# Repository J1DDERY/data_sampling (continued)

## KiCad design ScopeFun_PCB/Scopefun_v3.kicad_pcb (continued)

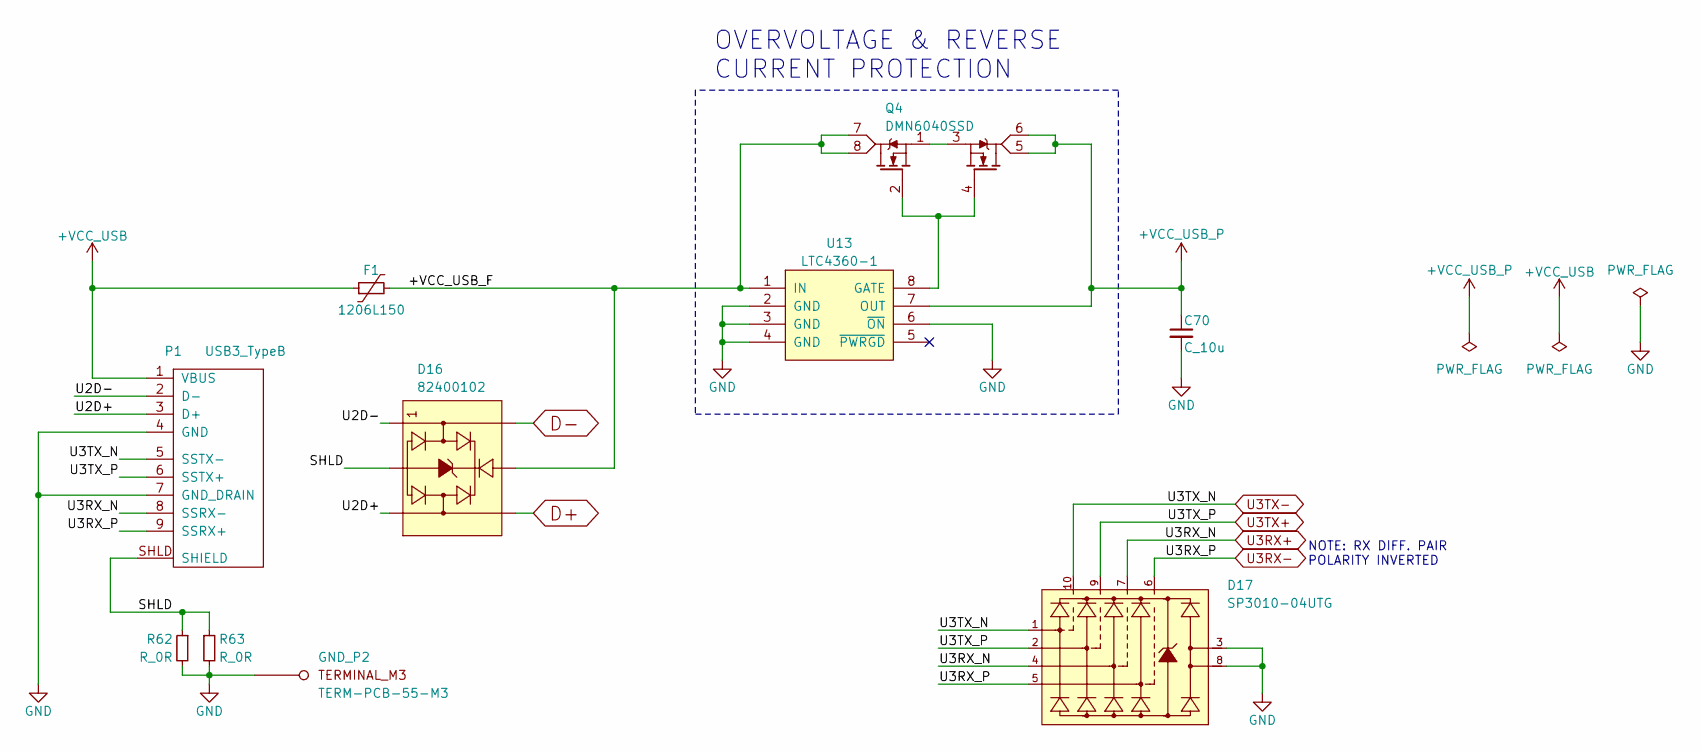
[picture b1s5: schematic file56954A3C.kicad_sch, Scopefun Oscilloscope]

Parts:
C70: C_10u; C_0603; MFG Part# GRM188R60J106KE47D
D16: 82400102; SOT23-6; MFG Part# 82400102
D17: SP3010-04UTG; uDFN-10; MFG Part# SP3010-04UTG
F1: 1206L150; R_1206; MFG Part# 1206L150THWR
GND_P2: TERM-PCB-55-M3; MFG Part# PCB-55(M3)
P1: USB3_TypeB; MFG Part# 692221030100
Q4: DMN6040SSD; SOIC8; MFG Part# DMN6040SSD-13
R62, R63: R_0R; R_0805; MFG Part# ERJ-6GEY0R00V
U13: LTC4360-1; SC70; MFG Part# LTC4360CSC8-1

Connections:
+VCC_USB: F1.1, P1.1 (VBUS)
+VCC_USB_P: C70.1, Q4.5 (D2), Q4.6 (D2), U13.7 (OUT); also elsewhere on the board
/USB Port/+VCC_USB_F: D16.5 (VDD), F1.2, Q4.7 (D1), Q4.8 (D1), U13.1 (IN)
/USB Port/SHLD: D16.2 (GND), P1.SHLD (SHIELD), R62.1, R63.1
/USB Port/U2D+: D16.3 (IO2), P1.3 (D+)
/USB Port/U2D-: D16.1 (IO1), P1.2 (D-)
D+: D16.4 (IO2); also elsewhere on the board
D-: D16.6 (IO1); also elsewhere on the board
GND: C70.2, D17.3 (IO2), D17.8 (IO1), GND_P2.1 (1_1), P1.4 (GND), P1.7 (GND_DRAIN), R62.2, R63.2, U13.2 (GND), U13.3 (GND), U13.4 (GND), U13.6 (~ON); also elsewhere on the board
unnamed: Q4.2 (G1), Q4.4 (G2), U13.8 (GATE)
unnamed: Q4.1 (S1), Q4.3 (S2)
U3RX+: D17.4 (IO2), D17.7 (IO1), P1.8 (SSRX-); also elsewhere on the board
U3RX-: D17.5 (VDD), D17.6 (IO1), P1.9 (SSRX+); also elsewhere on the board
U3TX+: D17.2 (GND), D17.9 (IO1), P1.6 (SSTX+); also elsewhere on the board
U3TX-: D17.1 (IO1), D17.10 (IO1), P1.5 (SSTX-); also elsewhere on the board

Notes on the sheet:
NOTE: RX DIFF. PAIR POLARITY INVERTED
OVERVOLTAGE & REVERSE CURRENT PROTECTION

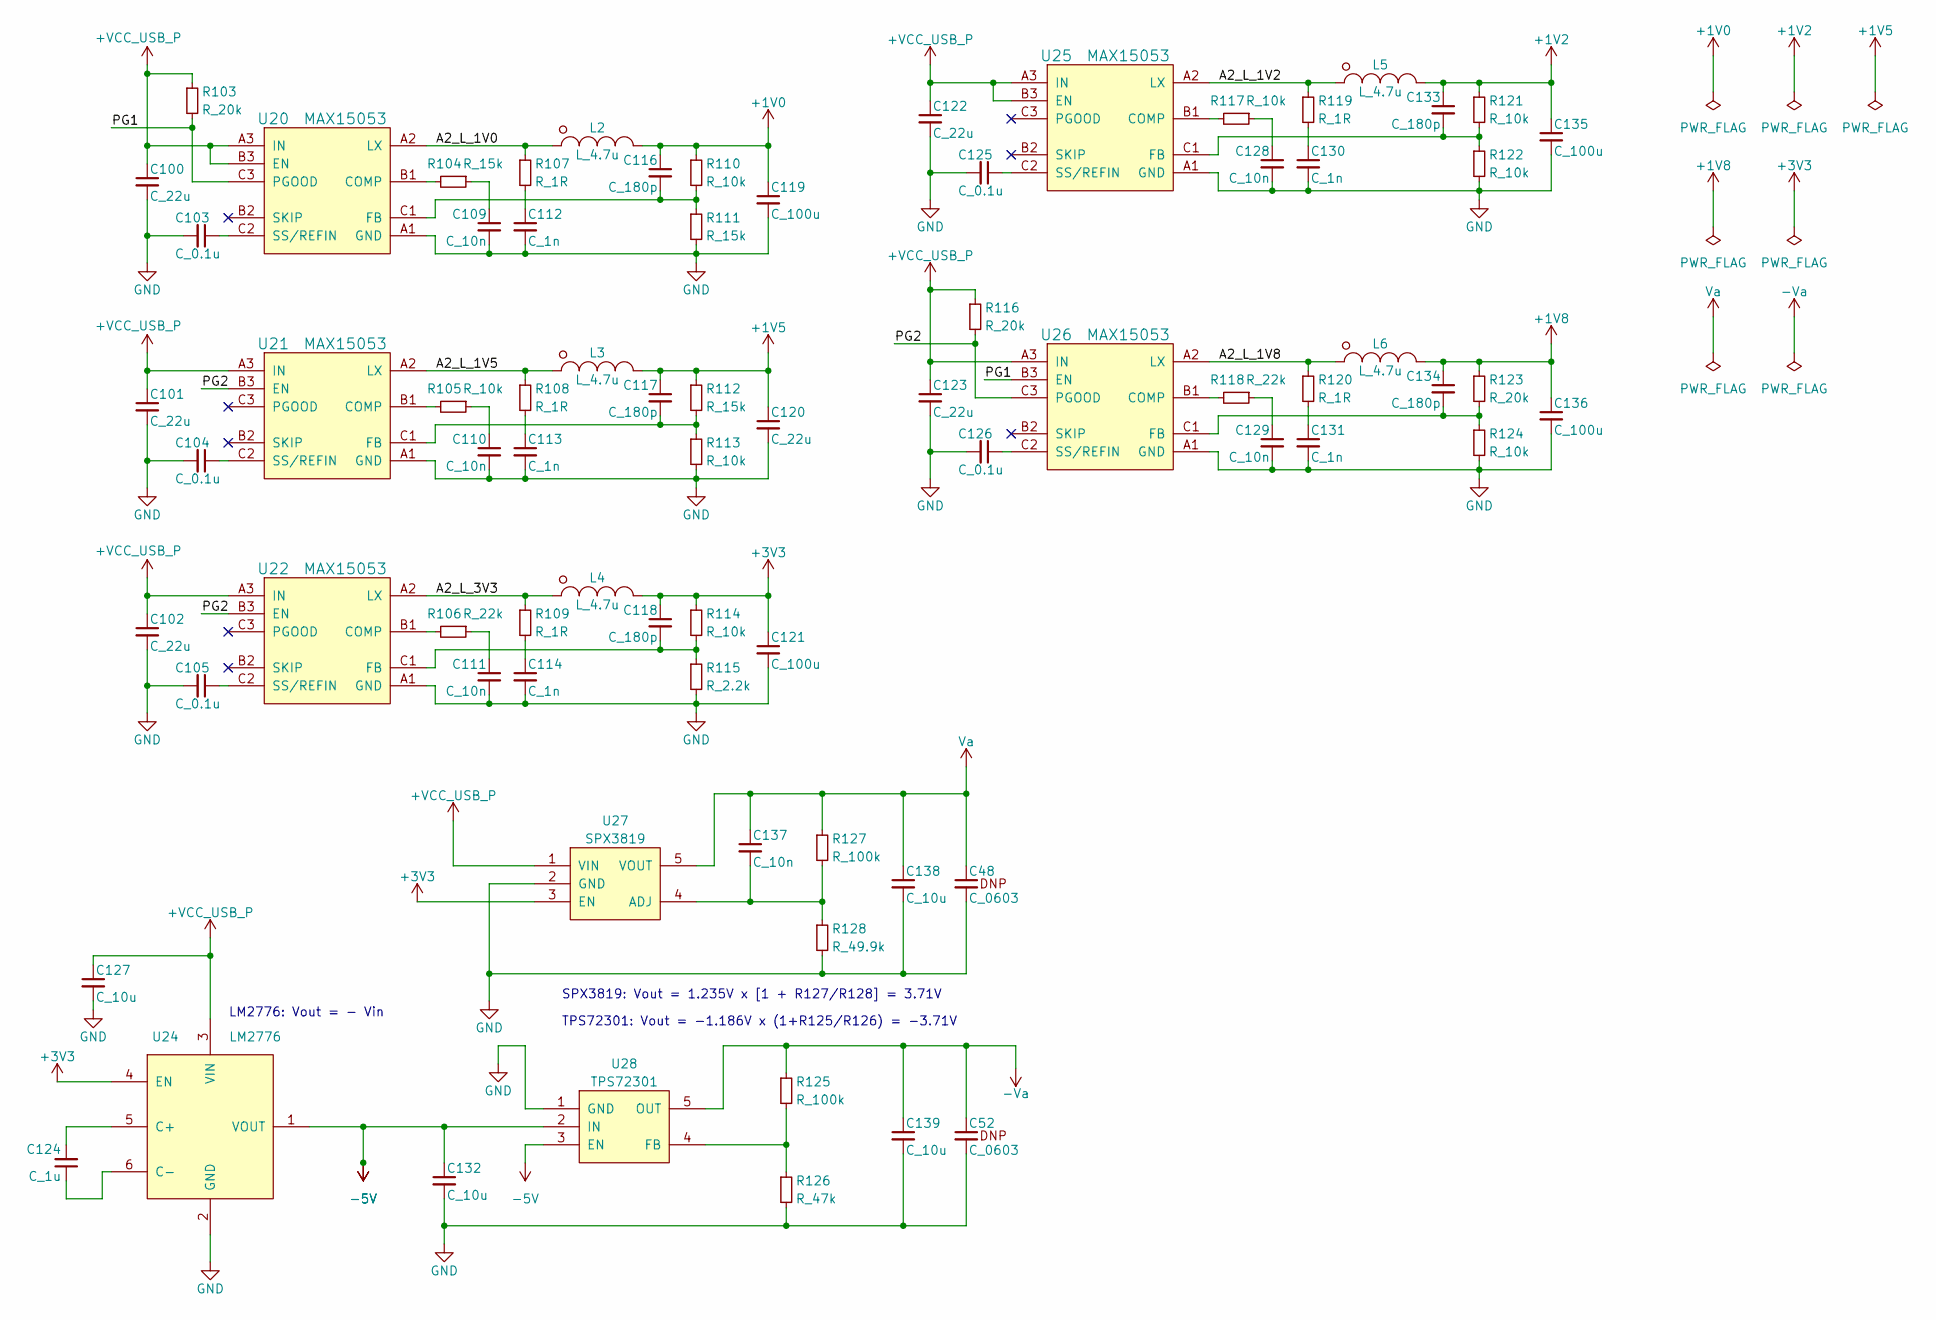
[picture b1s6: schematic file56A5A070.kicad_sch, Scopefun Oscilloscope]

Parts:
C48, C52: C_0603
C100, C101, C102, C120, C122, C123: C_22u; C_0805; MFG Part# LMK212BBJ226MG-T
C103, C104, C105, C125, C126: C_0.1u; C_0603; MFG Part# C0603C104K4RACTU
C109, C110, C111, C128, C129, C137: C_10n; C_0603; MFG Part# GRM1885C1H103JA01D
C112, C113, C114, C130, C131: C_1n; C_0603; MFG Part# C1608X7R1H102K080AE
C116, C117, C118, C133, C134: C_180p; C_0603; MFG Part# C0603C181J5GACTU
C119, C121, C135, C136: C_100u; C_1210; MFG Part# 12106D107MAT2A
C124: C_1u; C_0603; MFG Part# C0603C105K9PACTU
C127, C132, C138, C139: C_10u; C_0603; MFG Part# GRM188R60J106KE47D
L2, L3, L4, L5, L6: L_4.7u; L_NRS; MFG Part# NRS5030T4R7MMGJ
R103, R116, R123: R_20k; R_0603; MFG Part# ERJ-3EKF2002V
R104, R111, R112: R_15k; R_0603; MFG Part# ERJ-3EKF1502V
R105, R110, R113, R114, R117, R121, R122, R124: R_10k; R_0603; MFG Part# ERJ-3EKF1002V
R106, R118: R_22k; R_0603; MFG Part# ERJ-3EKF2202V
R107, R108, R109, R119, R120: R_1R; R_0603; MFG Part# ERJ-3GEYJ1R0V
R115: R_2.2k; R_0603; MFG Part# ERJ-3EKF2201V
R125, R127: R_100k; R_0603; MFG Part# ERJ-3EKF1003V
R126: R_47k; R_0603; MFG Part# ERJ-3EKF4702V
R128: R_49.9k; R_0603; MFG Part# ERJ-3EKF4992V
U20, U21, U22, U25, U26: MAX15053; WLP-9; MFG Part# MAX15053EWL+T
U24: LM2776; SOT23-6; MFG Part# LM2776DBVR
U27: SPX3819; SOT23-5_EXAR; MFG Part# SPX3819M5-L/TR
U28: TPS72301; SOT23-5; MFG Part# TPS72301DBVR

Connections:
+1V0: C116.1, C119.1, L2.2, R110.1; also elsewhere on the board
+1V2: C133.1, C135.1, L5.2, R121.1; also elsewhere on the board
+1V5: C117.1, C120.1, L3.2, R112.1; also elsewhere on the board
+1V8: C134.1, C136.1, L6.2, R123.1; also elsewhere on the board
+3V3: C118.1, C121.1, L4.2, R114.1, U24.4 (EN), U27.3 (EN); also elsewhere on the board
+VCC_USB_P: C100.1, C101.1, C102.1, C122.1, C123.1, C127.1, R103.1, R116.1, U20.A3 (IN), U20.B3 (EN), U21.A3 (IN), U22.A3 (IN), U24.3 (VIN), U25.A3 (IN), U25.B3 (EN), U26.A3 (IN), U27.1 (VIN); also elsewhere on the board
-5V: C132.1, U24.1 (VOUT), U28.2 (IN), U28.3 (EN)
-Va: C52.1, C139.1, R125.1, U28.5 (OUT); also elsewhere on the board
/POWER SUPPLY/A2_L_1V0: L2.1, R107.1, U20.A2 (LX)
/POWER SUPPLY/A2_L_1V2: L5.1, R119.1, U25.A2 (LX)
/POWER SUPPLY/A2_L_1V5: L3.1, R108.1, U21.A2 (LX)
/POWER SUPPLY/A2_L_1V8: L6.1, R120.1, U26.A2 (LX)
/POWER SUPPLY/A2_L_3V3: L4.1, R109.1, U22.A2 (LX)
/POWER SUPPLY/PG1: R103.2, U20.C3 (PGOOD), U26.B3 (EN)
/POWER SUPPLY/PG2: R116.2, U21.B3 (EN), U22.B3 (EN), U26.C3 (PGOOD)
GND: C48.2, C52.2, C100.2, C101.2, C102.2, C103.2, C104.2, C105.2, C109.2, C110.2, C111.2, C112.2, C113.2, C114.2, C119.2, C120.2, C121.2, C122.2, C123.2, C125.2, C126.2, C127.2, C128.2, C129.2, C130.2, C131.2, C132.2, C135.2, C136.2, C138.2, C139.2, R111.2, R113.2, R115.2, R122.2, R124.2, R126.2, R128.2, U20.A1 (GND), U21.A1 (GND), U22.A1 (GND), U24.2 (GND), U25.A1 (GND), U26.A1 (GND), U27.2 (GND), U28.1 (GND); also elsewhere on the board
unnamed: C109.1, R104.1
unnamed: C110.1, R105.1
unnamed: C111.1, R106.1
unnamed: C112.1, R107.2
unnamed: C113.1, R108.2
unnamed: C114.1, R109.2
unnamed: C128.1, R117.1
unnamed: C129.1, R118.1
unnamed: C130.1, R119.2
unnamed: C131.1, R120.2
unnamed: R104.2, U20.B1 (COMP)
unnamed: C116.2, R110.2, R111.1, U20.C1 (FB)
unnamed: C103.1, U20.C2 (SS/REFIN)
unnamed: R105.2, U21.B1 (COMP)
unnamed: C117.2, R112.2, R113.1, U21.C1 (FB)
unnamed: C104.1, U21.C2 (SS/REFIN)
unnamed: R106.2, U22.B1 (COMP)
unnamed: C118.2, R114.2, R115.1, U22.C1 (FB)
unnamed: C105.1, U22.C2 (SS/REFIN)
unnamed: C124.2, U24.5 (C+)
unnamed: C124.1, U24.6 (C-)
unnamed: R117.2, U25.B1 (COMP)
unnamed: C133.2, R121.2, R122.1, U25.C1 (FB)
unnamed: C125.1, U25.C2 (SS/REFIN)
unnamed: R118.2, U26.B1 (COMP)
unnamed: C134.2, R123.2, R124.1, U26.C1 (FB)
unnamed: C126.1, U26.C2 (SS/REFIN)
unnamed: C137.2, R127.2, R128.1, U27.4 (ADJ)
unnamed: R125.2, R126.1, U28.4 (FB)
Va: C48.1, C137.1, C138.1, R127.1, U27.5 (VOUT); also elsewhere on the board

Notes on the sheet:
SPX3819: Vout = 1.235V x [1 + R127/R128] = 3.71V
TPS72301: Vout = -1.186V x (1+R125/R126) = -3.71V
LM2776: Vout = - Vin

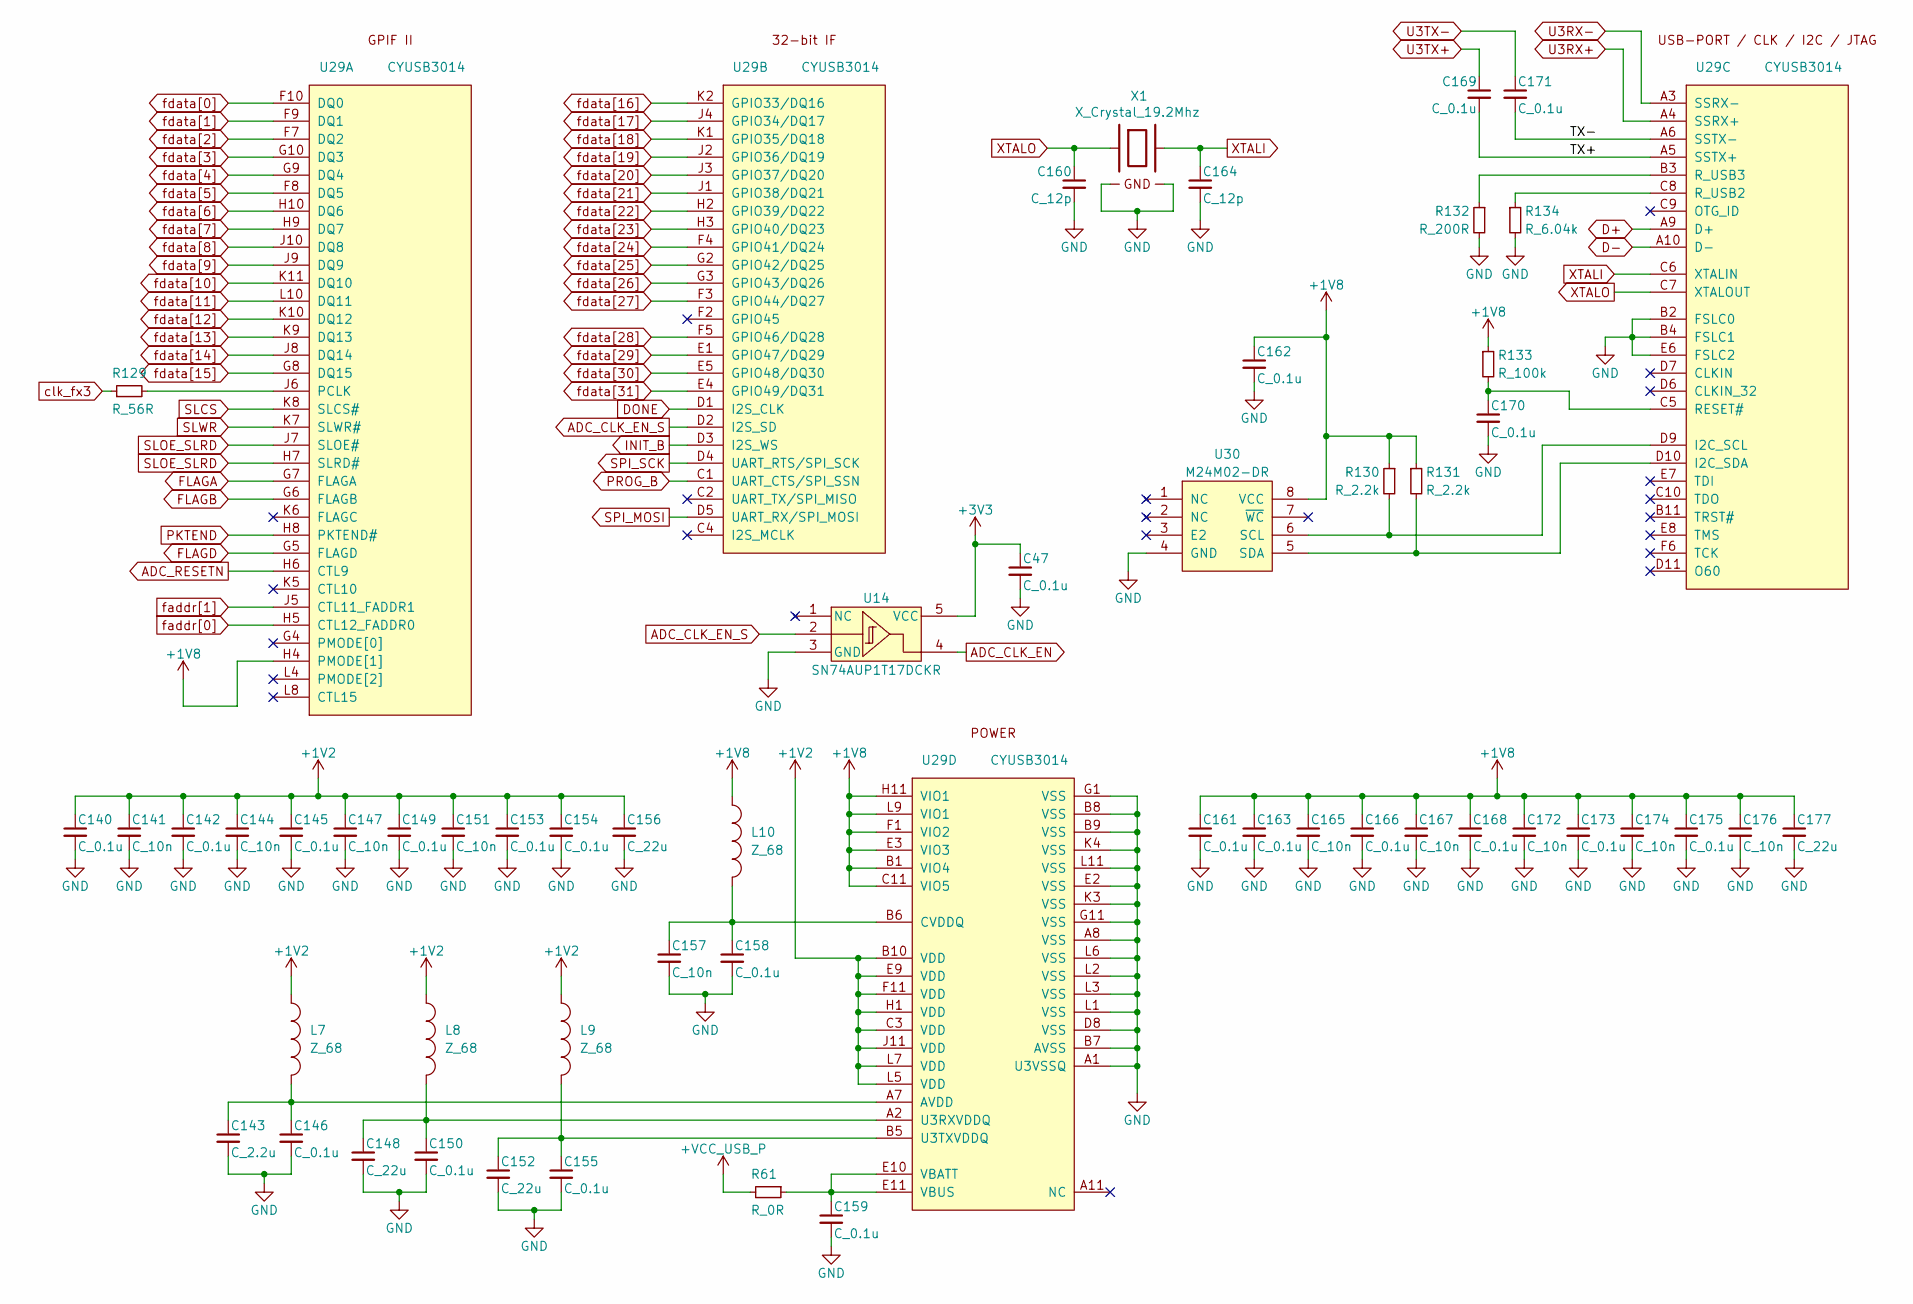
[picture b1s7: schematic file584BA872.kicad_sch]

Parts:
C47, C140, C142, C145, C146, C149, C150, C153, C154, C155, C158, C159, C161, C162, C163, C166, C168, C170, C173, C175: C_0.1u; C_0603; MFG Part# C0603C104K4RACTU
C141, C144, C147, C151, C157, C165, C167, C172, C174, C176: C_10n; C_0603; MFG Part# GRM1885C1H103JA01D
C143: C_2.2u; C_0603; MFG Part# CC0603MRX5R5BB225
C148, C152, C156, C177: C_22u; C_0805; MFG Part# LMK212BBJ226MG-T
C160, C164: C_12p; C_0603; MFG Part# CGA3E2C0G1H120J080AA
C169, C171: C_0.1u; C_0402; MFG Part# 885012205018
L7, L8, L9, L10: Z_68; L_0805; MFG Part# 782853680
R61: R_0R; R_0805; MFG Part# ERJ-6GEY0R00V
R129: R_56R; R_0603; MFG Part# ERJ-3EKF56R0V
R130, R131: R_2.2k; R_0603; MFG Part# ERJ-3EKF2201V
R132: R_200R; R_0603; MFG Part# ERJ-3EKF2000V
R133: R_100k; R_0603; MFG Part# ERJ-3EKF1003V
R134: R_6.04k; R_0603; MFG Part# ERJ-3EKF6041V
U14: SN74AUP1T17DCKR; SC70-5; MFG Part# SN74AUP1T17DCKR
U29: CYUSB3014; BGA121_0.8mm; MFG Part# CYUSB3014-BZXC
U30: M24M02-DR; SOIC8; MFG Part# M24M02-DRMN6TP
X1: X_Crystal_19.2Mhz; XTAL-4; MFG Part# FL1920031

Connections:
+1V2: C140.1, C141.1, C142.1, C144.1, C145.1, C147.1, C149.1, C151.1, C153.1, C154.1, C156.1, L7.1, L8.1, L9.1, U29.B10 (VDD), U29.C3 (VDD), U29.E9 (VDD), U29.F11 (VDD), U29.H1 (VDD), U29.J11 (VDD), U29.L5 (VDD), U29.L7 (VDD); also elsewhere on the board
+1V8: C161.1, C162.1, C163.1, C165.1, C166.1, C167.1, C168.1, C172.1, C173.1, C174.1, C175.1, C176.1, C177.1, L10.1, R130.1, R131.1, R133.1, U29.B1 (VIO4), U29.C11 (VIO5), U29.E3 (VIO3), U29.F1 (VIO2), U29.H4 (PMODE[1]), U29.H11 (VIO1), U29.L9 (VIO1), U30.8 (VCC); also elsewhere on the board
+3V3: C47.1, U14.5 (VCC); also elsewhere on the board
+VCC_USB_P: R61.2; also elsewhere on the board
/USB FX3/TX+: C169.2, U29.A5 (SSTX+)
/USB FX3/TX-: C171.2, U29.A6 (SSTX-)
ADC_CLK_EN: U14.4; also elsewhere on the board
ADC_CLK_EN_S: U14.2, U29.D2 (I2S_SD)
ADC_RESETN: U29.H6 (CTL9); also elsewhere on the board
D+: U29.A9 (D+); also elsewhere on the board
D-: U29.A10 (D-); also elsewhere on the board
DONE: U29.D1 (I2S_CLK); also elsewhere on the board
FLAGA: U29.G7 (FLAGA); also elsewhere on the board
FLAGB: U29.G6 (FLAGB); also elsewhere on the board
FLAGD: U29.G5 (FLAGD); also elsewhere on the board
GND: C47.2, C140.2, C141.2, C142.2, C143.2, C144.2, C145.2, C146.2, C147.2, C148.2, C149.2, C150.2, C151.2, C152.2, C153.2, C154.2, C155.2, C156.2, C157.2, C158.2, C159.2, C160.2, C161.2, C162.2, C163.2, C164.2, C165.2, C166.2, C167.2, C168.2, C170.2, C172.2, C173.2, C174.2, C175.2, C176.2, C177.2, R132.2, R134.2, U14.3 (GND), U29.A1 (U3VSSQ), U29.A8 (VSS), U29.B2 (FSLC0), U29.B4 (FSLC1), U29.B7 (AVSS), U29.B8 (VSS), U29.B9 (VSS), U29.D8 (VSS), U29.E2 (VSS), U29.E6 (FSLC2), U29.G1 (VSS), U29.G11 (VSS), U29.K3 (VSS), U29.K4 (VSS), U29.L1 (VSS), U29.L2 (VSS), U29.L3 (VSS), U29.L6 (VSS), U29.L11 (VSS), U30.4 (GND), X1.2 (GND), X1.4 (GND); also elsewhere on the board
INIT_B: U29.D3 (I2S_WS); also elsewhere on the board
unnamed: R129.2, U29.J6 (PCLK)
unnamed: R130.2, U29.D9 (I2C_SCL), U30.6 (SCL)
unnamed: R131.2, U29.D10 (I2C_SDA), U30.5 (SDA)
unnamed: C170.1, R133.2, U29.C5 (RESET#)
unnamed: R134.1, U29.C8 (R_USB2)
unnamed: R132.1, U29.B3 (R_USB3)
unnamed: C143.1, C146.1, L7.2, U29.A7 (AVDD)
unnamed: C157.1, C158.1, L10.2, U29.B6 (CVDDQ)
unnamed: C148.1, C150.1, L8.2, U29.A2 (U3RXVDDQ)
unnamed: C152.1, C155.1, L9.2, U29.B5 (U3TXVDDQ)
unnamed: C159.1, R61.1, U29.E10 (VBATT), U29.E11 (VBUS)
PKTEND: U29.H8 (PKTEND#); also elsewhere on the board
PROG_B: U29.C1 (UART_CTS/SPI_SSN); also elsewhere on the board
SLCS: U29.K8 (SLCS#); also elsewhere on the board
SLOE_SLRD: U29.H7 (SLRD#), U29.J7 (SLOE#); also elsewhere on the board
SLWR: U29.K7 (SLWR#); also elsewhere on the board
SPI_MOSI: U29.D5 (UART_RX/SPI_MOSI); also elsewhere on the board
SPI_SCK: U29.D4 (UART_RTS/SPI_SCK); also elsewhere on the board
U3RX+: U29.A4 (SSRX+); also elsewhere on the board
U3RX-: U29.A3 (SSRX-); also elsewhere on the board
U3TX+: C169.1; also elsewhere on the board
U3TX-: C171.1; also elsewhere on the board
XTALI: C164.1, U29.C6 (XTALIN), X1.3
XTALO: C160.1, U29.C7 (XTALOUT), X1.1
clk_fx3: R129.1; also elsewhere on the board
faddr[0]: U29.H5 (CTL12_FADDR0); also elsewhere on the board
faddr[1]: U29.J5 (CTL11_FADDR1); also elsewhere on the board
fdata[0]: U29.F10 (DQ0); also elsewhere on the board
fdata[1]: U29.F9 (DQ1); also elsewhere on the board
fdata[2]: U29.F7 (DQ2); also elsewhere on the board
fdata[3]: U29.G10 (DQ3); also elsewhere on the board
fdata[4]: U29.G9 (DQ4); also elsewhere on the board
fdata[5]: U29.F8 (DQ5); also elsewhere on the board
fdata[6]: U29.H10 (DQ6); also elsewhere on the board
fdata[7]: U29.H9 (DQ7); also elsewhere on the board
fdata[8]: U29.J10 (DQ8); also elsewhere on the board
fdata[9]: U29.J9 (DQ9); also elsewhere on the board
fdata[10]: U29.K11 (DQ10); also elsewhere on the board
fdata[11]: U29.L10 (DQ11); also elsewhere on the board
fdata[12]: U29.K10 (DQ12); also elsewhere on the board
fdata[13]: U29.K9 (DQ13); also elsewhere on the board
fdata[14]: U29.J8 (DQ14); also elsewhere on the board
fdata[15]: U29.G8 (DQ15); also elsewhere on the board
fdata[16]: U29.K2 (GPIO33/DQ16); also elsewhere on the board
fdata[17]: U29.J4 (GPIO34/DQ17); also elsewhere on the board
fdata[18]: U29.K1 (GPIO35/DQ18); also elsewhere on the board
fdata[19]: U29.J2 (GPIO36/DQ19); also elsewhere on the board
fdata[20]: U29.J3 (GPIO37/DQ20); also elsewhere on the board
fdata[21]: U29.J1 (GPIO38/DQ21); also elsewhere on the board
fdata[22]: U29.H2 (GPIO39/DQ22); also elsewhere on the board
fdata[23]: U29.H3 (GPIO40/DQ23); also elsewhere on the board
fdata[24]: U29.F4 (GPIO41/DQ24); also elsewhere on the board
fdata[25]: U29.G2 (GPIO42/DQ25); also elsewhere on the board
fdata[26]: U29.G3 (GPIO43/DQ26); also elsewhere on the board
fdata[27]: U29.F3 (GPIO44/DQ27); also elsewhere on the board
fdata[28]: U29.F5 (GPIO46/DQ28); also elsewhere on the board
fdata[29]: U29.E1 (GPIO47/DQ29); also elsewhere on the board
fdata[30]: U29.E5 (GPIO48/DQ30); also elsewhere on the board
fdata[31]: U29.E4 (GPIO49/DQ31); also elsewhere on the board

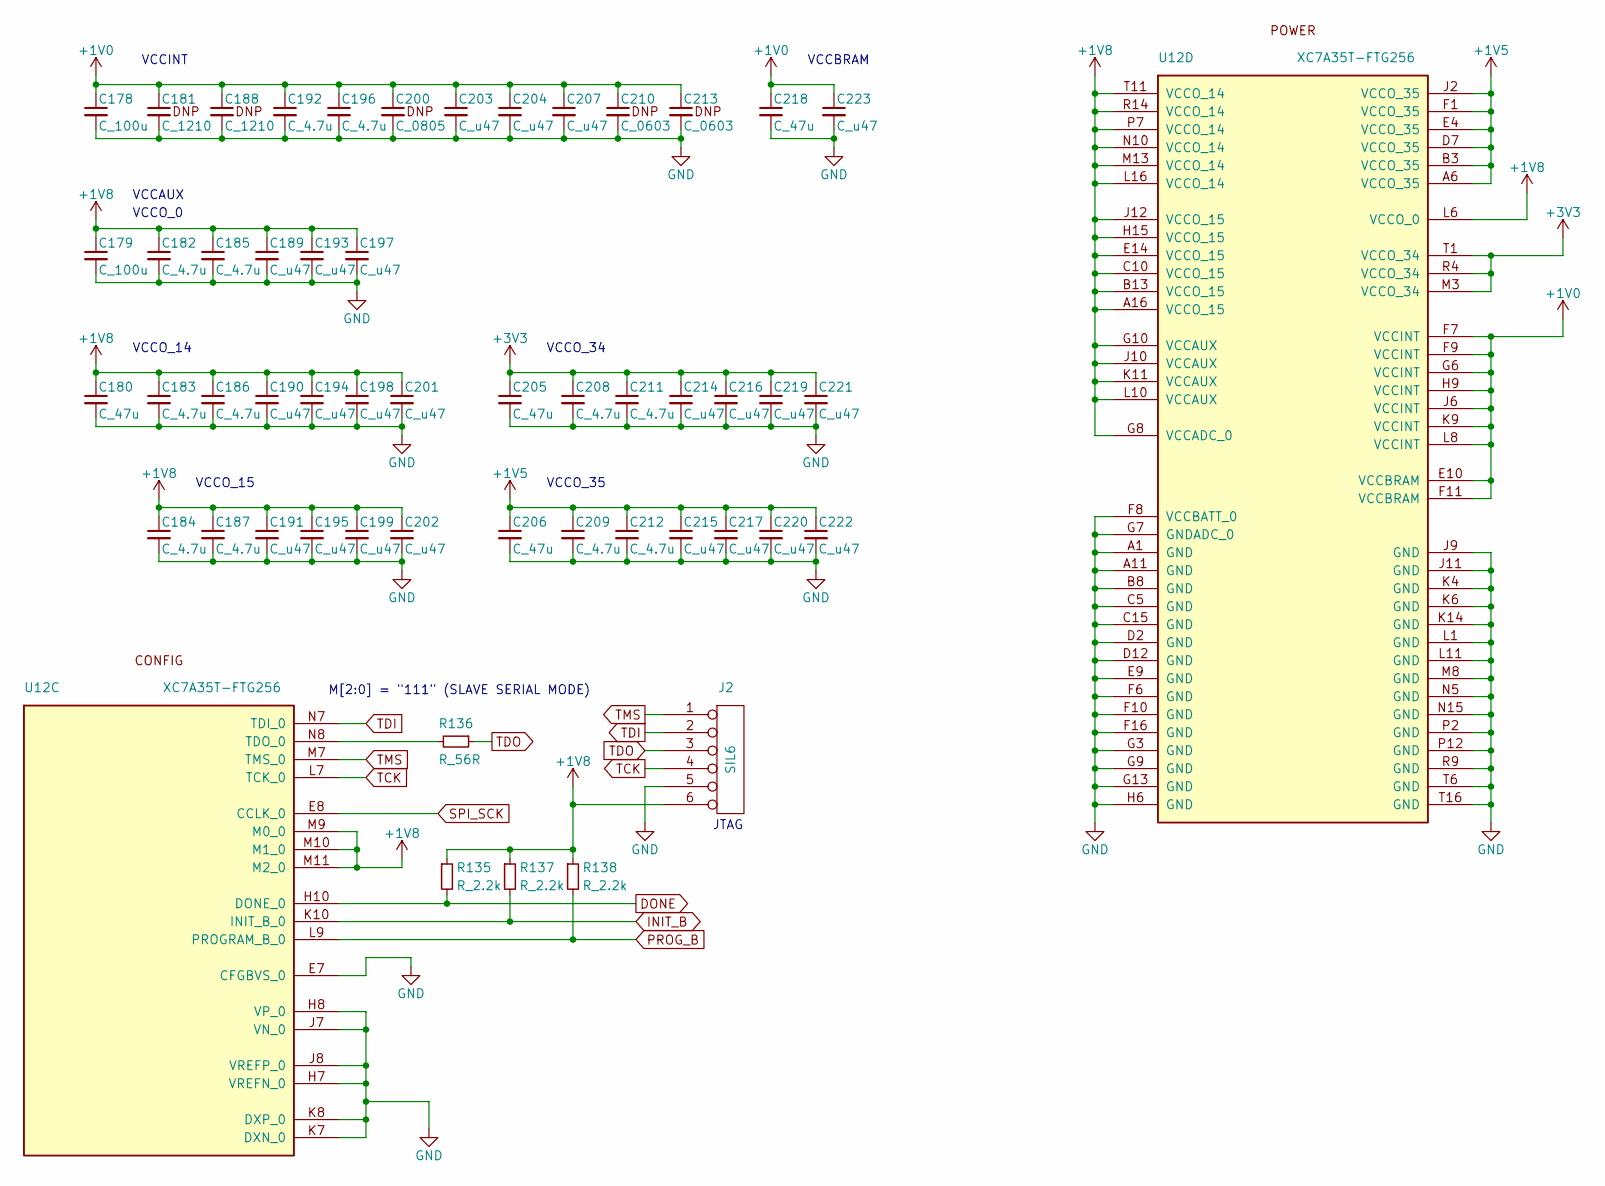
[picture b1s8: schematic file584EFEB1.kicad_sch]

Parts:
C178, C179: C_100u; C_1210; MFG Part# 12106D107MAT2A
C180, C205, C206, C218: C_47u; C_1210; MFG Part# LMK325BJ476MM-T
C181, C188: C_1210
C182, C183, C184, C185, C186, C187, C192, C196, C208, C209, C211, C212: C_4.7u; C_0805; MFG Part# C2012X7R1A475K125AC
C189, C191, C193, C194, C195, C197, C198, C199, C201, C202, C203, C204, C207, C214, C215, C216, C217, C219, C220, C221, C222, C223: C_u47; C_0603; MFG Part# EMK107B7474KA-T
C190: C_u47; C_0603; MFG Part# EMK107B7474KA-T; jlc C6119831
C200: C_0805
C210, C213: C_0603
J2: SIL6; MFG Part# M20-9990645
R135, R137, R138: R_2.2k; R_0603; MFG Part# ERJ-3EKF2201V
R136: R_56R; R_0603; MFG Part# ERJ-3EKF56R0V
U12: XC7A35T-FTG256; BGA256_FTG256; MFG Part# XC7A35T-2FTG256I

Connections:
+1V0: C178.1, C181.1, C188.1, C192.1, C196.1, C200.1, C203.1, C204.1, C207.1, C210.1, C213.1, C218.1, C223.1, U12.E10 (VCCBRAM), U12.F7 (VCCINT), U12.F9 (VCCINT), U12.F11 (VCCBRAM), U12.G6 (VCCINT), U12.H9 (VCCINT), U12.J6 (VCCINT), U12.K9 (VCCINT), U12.L8 (VCCINT); also elsewhere on the board
+1V5: C206.1, C209.1, C212.1, C215.1, C217.1, C220.1, C222.1, U12.A6 (VCCO_35), U12.B3 (VCCO_35), U12.D7 (VCCO_35), U12.E4 (VCCO_35), U12.F1 (VCCO_35), U12.J2 (VCCO_35); also elsewhere on the board
+1V8: C179.1, C180.1, C182.1, C183.1, C184.1, C185.1, C186.1, C187.1, C189.1, C190.1, C191.1, C193.1, C194.1, C195.1, C197.1, C198.1, C199.1, C201.1, C202.1, J2.6, R135.1, R137.1, R138.1, U12.A16 (VCCO_15), U12.B13 (VCCO_15), U12.C10 (VCCO_15), U12.E14 (VCCO_15), U12.G8 (VCCADC_0), U12.G10 (VCCAUX), U12.H15 (VCCO_15), U12.J10 (VCCAUX), U12.J12 (VCCO_15), U12.K11 (VCCAUX), U12.L6 (VCCO_0), U12.L10 (VCCAUX), U12.L16 (VCCO_14), U12.M9 (M0_0), U12.M10 (M1_0), U12.M11 (M2_0), U12.M13 (VCCO_14), U12.N10 (VCCO_14), U12.P7 (VCCO_14), U12.R14 (VCCO_14), U12.T11 (VCCO_14); also elsewhere on the board
+3V3: C205.1, C208.1, C211.1, C214.1, C216.1, C219.1, C221.1, U12.M3 (VCCO_34), U12.R4 (VCCO_34), U12.T1 (VCCO_34); also elsewhere on the board
DONE: R135.2, U12.H10 (DONE_0); also elsewhere on the board
GND: C178.2, C179.2, C180.2, C181.2, C182.2, C183.2, C184.2, C185.2, C186.2, C187.2, C188.2, C189.2, C190.2, C191.2, C192.2, C193.2, C194.2, C195.2, C196.2, C197.2, C198.2, C199.2, C200.2, C201.2, C202.2, C203.2, C204.2, C205.2, C206.2, C207.2, C208.2, C209.2, C210.2, C211.2, C212.2, C213.2, C214.2, C215.2, C216.2, C217.2, C218.2, C219.2, C220.2, C221.2, C222.2, C223.2, J2.5, U12.A1 (GND), U12.A11 (GND), U12.B8 (GND), U12.C5 (GND), U12.C15 (GND), U12.D2 (GND), U12.D12 (GND), U12.E7 (CFGBVS_0), U12.E9 (GND), U12.F6 (GND), U12.F8 (VCCBATT_0), U12.F10 (GND), U12.F16 (GND), U12.G3 (GND), U12.G7 (GNDADC_0), U12.G9 (GND), U12.G13 (GND), U12.H6 (GND), U12.H7 (VREFN_0), U12.H8 (VP_0), U12.J7 (VN_0), U12.J8 (VREFP_0), U12.J9 (GND), U12.J11 (GND), U12.K4 (GND), U12.K6 (GND), U12.K7 (DXN_0), U12.K8 (DXP_0), U12.K14 (GND), U12.L1 (GND), U12.L11 (GND), U12.M8 (GND), U12.N5 (GND), U12.N15 (GND), U12.P2 (GND), U12.P12 (GND), U12.R9 (GND), U12.T6 (GND), U12.T16 (GND); also elsewhere on the board
INIT_B: R137.2, U12.K10 (INIT_B_0); also elsewhere on the board
unnamed: R136.2, U12.N8 (TDO_0)
PROG_B: R138.2, U12.L9 (PROGRAM_B_0); also elsewhere on the board
SPI_SCK: U12.E8 (CCLK_0); also elsewhere on the board
TCK: J2.4, U12.L7 (TCK_0)
TDI: J2.2, U12.N7 (TDI_0)
TDO: J2.3, R136.1
TMS: J2.1, U12.M7 (TMS_0)

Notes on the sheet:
JTAG
VCCINT
M[2:0] = "111" (SLAVE SERIAL MODE)
VCCBRAM
VCCO_14
VCCO_15
VCCO_34
VCCO_0
VCCAUX
VCCO_35

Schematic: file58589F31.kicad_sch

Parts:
C241, C242, C243: C_10u; C_0603; MFG Part# GRM188R60J106KE47D
D55, D56: LM431; SOT23; MFG Part# LM431SBCM32X
D57: TLV431A; SOT23; MFG Part# TLV431ASN1T1G
R163, R164, R167, R169, R171, R173: R_1.02k; R_0603; MFG Part# ERJ-3EKF1021V
R168, R170: R_6.8k; R_0603; MFG Part# ERJ-3EKF6801V
R172: R_200R; R_0603; MFG Part# ERJ-3EKF2000V

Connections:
+1.48V: C243.1, D57.2 (C), R171.1, R172.1; also elsewhere on the board
+2.88V: C241.1, D55.1 (C), R163.1, R167.1; also elsewhere on the board
-2.88V: C242.2, D56.3 (A), R164.1, R170.2; also elsewhere on the board
-Va: R164.2; also elsewhere on the board
GND: C241.2, C242.1, C243.2, D55.3 (A), D56.1 (C), D57.3 (A), R168.2, R169.1, R173.2; also elsewhere on the board
unnamed: D55.2 (REF), R167.2, R168.1
unnamed: D56.2 (REF), R169.2, R170.1
unnamed: D57.1 (REF), R172.2, R173.1
Va: R163.2, R171.2; also elsewhere on the board

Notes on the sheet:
LM431: Vout=2.5V*(1+Ra/Rb)

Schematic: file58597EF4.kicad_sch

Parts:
C244, C245: C_22u; C_0805; MFG Part# LMK212BBJ226MG-T
C246, C247, C248, C249, C251, C252, C255, C256: C_0.1u; C_0603; MFG Part# C0603C104K4RACTU
C250: C_1u; C_0603; MFG Part# C0603C105K9PACTU
C253, C254: C_10n; C_0603; MFG Part# GRM1885C1H103JA01D
R174, R175, R176, R177, R178, R179: RA_27R; R_CRA06E; MFG Part# YC164-JR-0727RL
R180: R_240R; R_0603; MFG Part# ERJ-3EKF2400V
R181, R183, R184: R_100; R_0402; MFG Part# ERJ-2RKF1000X
R182: R_4k7; R_0603; MFG Part# ERJ-3EKF4701V
R185, R186: R_1.02k; R_0603; MFG Part# ERJ-3EKF1021V
U36: IS43TR16256B-125KBL; TW-BGA-96; MFG Part# IS43TR16640B-125JBL

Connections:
+1V5: C244.1, C245.1, C246.1, C247.1, C248.1, C249.1, C251.1, C252.1, C253.1, C255.1, C256.1, R185.1, U36.A1 (VDDQ), U36.A8 (VDDQ), U36.B2 (VDD), U36.C1 (VDDQ), U36.C9 (VDDQ), U36.D2 (VDDQ), U36.D9 (VDD), U36.E9 (VDDQ), U36.F1 (VDDQ), U36.G7 (VDD), U36.H2 (VDDQ), U36.H9 (VDDQ), U36.K2 (VDD), U36.K8 (VDD), U36.N1 (VDD), U36.N9 (VDD), U36.R1 (VDD), U36.R9 (VDD); also elsewhere on the board
/DDR3 SDRAM/DDR3_A0_: R174.3, U36.N3 (A0)
/DDR3 SDRAM/DDR3_A1_: R177.1, U36.P7 (A1)
/DDR3 SDRAM/DDR3_A2_: R175.1, U36.P3 (A2)
/DDR3 SDRAM/DDR3_A3_: R175.2, U36.N2 (A3)
/DDR3 SDRAM/DDR3_A4_: R179.3, U36.P8 (A4)
/DDR3 SDRAM/DDR3_A5_: R174.4, U36.P2 (A5)
/DDR3 SDRAM/DDR3_A6_: R178.2, U36.R8 (A6)
/DDR3 SDRAM/DDR3_A7_: R174.1, U36.R2 (A7)
/DDR3 SDRAM/DDR3_A8_: R178.1, U36.T8 (A8)
/DDR3 SDRAM/DDR3_A9_: R176.3, U36.R3 (A9)
/DDR3 SDRAM/DDR3_A10_: R178.3, U36.L7 (A10/AP)
/DDR3 SDRAM/DDR3_A11_: R177.3, U36.R7 (A11)
/DDR3 SDRAM/DDR3_A12_: R179.1, U36.N7 (A12/~BC)
/DDR3 SDRAM/DDR3_A13_: R176.4, U36.T3 (A13)
/DDR3 SDRAM/DDR3_A14_: R177.4, U36.T7 (A14)
/DDR3 SDRAM/DDR3_BA0_: R175.3, U36.M2 (BA0)
/DDR3 SDRAM/DDR3_BA1_: R179.2, U36.N8 (BA1)
/DDR3 SDRAM/DDR3_BA2_: R177.2, U36.M3 (BA2)
/DDR3 SDRAM/DDR3_CAS#_: R175.4, U36.K3 (~CAS)
/DDR3 SDRAM/DDR3_CKE_: R178.4, U36.K9 (CKE)
/DDR3 SDRAM/DDR3_ODT_: R176.1, U36.K1 (ODT)
/DDR3 SDRAM/DDR3_RAS#_: R176.2, U36.J3 (~RAS)
/DDR3 SDRAM/DDR3_WE#_: R174.2, U36.L3 (~WE)
/DDR3 SDRAM/VFREF: C250.1, C253.2, C254.1, R185.2, R186.1, U36.H1 (VREFDQ), U36.M8 (VREFCA)
DDR3_A0: R174.6; also elsewhere on the board
DDR3_A1: R177.8; also elsewhere on the board
DDR3_A2: R175.8; also elsewhere on the board
DDR3_A3: R175.7; also elsewhere on the board
DDR3_A4: R179.6; also elsewhere on the board
DDR3_A5: R174.5; also elsewhere on the board
DDR3_A6: R178.7; also elsewhere on the board
DDR3_A7: R174.8; also elsewhere on the board
DDR3_A8: R178.8; also elsewhere on the board
DDR3_A9: R176.6; also elsewhere on the board
DDR3_A10: R178.6; also elsewhere on the board
DDR3_A11: R177.6; also elsewhere on the board
DDR3_A12: R179.8; also elsewhere on the board
DDR3_A13: R176.5; also elsewhere on the board
DDR3_A14: R177.5; also elsewhere on the board
DDR3_BA0: R175.6; also elsewhere on the board
DDR3_BA1: R179.7; also elsewhere on the board
DDR3_BA2: R177.7; also elsewhere on the board
DDR3_CAS#: R175.5; also elsewhere on the board
DDR3_CKE: R178.5; also elsewhere on the board
DDR3_CK_N: R181.2, U36.K7 (~CK); also elsewhere on the board
DDR3_CK_P: R181.1, U36.J7 (CK); also elsewhere on the board
DDR3_DQ0: U36.E3 (DQL0); also elsewhere on the board
DDR3_DQ1: U36.F7 (DQL1); also elsewhere on the board
DDR3_DQ2: U36.F2 (DQL2); also elsewhere on the board
DDR3_DQ3: U36.F8 (DQL3); also elsewhere on the board
DDR3_DQ4: U36.H3 (DQL4); also elsewhere on the board
DDR3_DQ5: U36.H8 (DQL5); also elsewhere on the board
DDR3_DQ6: U36.G2 (DQL6); also elsewhere on the board
DDR3_DQ7: U36.H7 (DQL7); also elsewhere on the board
DDR3_DQ8: U36.D7 (DQU0); also elsewhere on the board
DDR3_DQ9: U36.C3 (DQU1); also elsewhere on the board
DDR3_DQ10: U36.C8 (DQU2); also elsewhere on the board
DDR3_DQ11: U36.C2 (DQU3); also elsewhere on the board
DDR3_DQ12: U36.A7 (DQU4); also elsewhere on the board
DDR3_DQ13: U36.A2 (DQU5); also elsewhere on the board
DDR3_DQ14: U36.B8 (DQU6); also elsewhere on the board
DDR3_DQ15: U36.A3 (DQU7); also elsewhere on the board
DDR3_DQS0_N: R183.2, U36.G3 (~DQSL); also elsewhere on the board
DDR3_DQS0_P: R183.1, U36.F3 (DQSL); also elsewhere on the board
DDR3_DQS1_N: R184.2, U36.B7 (~DQSU); also elsewhere on the board
DDR3_DQS1_P: R184.1, U36.C7 (DQSU); also elsewhere on the board
DDR3_ODT: R176.8; also elsewhere on the board
DDR3_RAS#: R176.7; also elsewhere on the board
DDR3_RESET#: R182.1, U36.T2 (~RESET); also elsewhere on the board
DDR3_WE#: R174.7; also elsewhere on the board
GND: C244.2, C245.2, C246.2, C247.2, C248.2, C249.2, C250.2, C251.2, C252.2, C254.2, C255.2, C256.2, R180.2, R182.2, R186.2, U36.A9 (VSS), U36.B1 (VSSQ), U36.B3 (VSS), U36.B9 (VSSQ), U36.D1 (VSSQ), U36.D3 (DMU), U36.D8 (VSSQ), U36.E1 (VSS), U36.E2 (VSSQ), U36.E7 (DML), U36.E8 (VSSQ), U36.F9 (VSSQ), U36.G1 (VSSQ), U36.G8 (VSS), U36.G9 (VSSQ), U36.J2 (VSS), U36.J8 (VSS), U36.L2 (~CS), U36.M1 (VSS), U36.M9 (VSS), U36.P1 (VSS), U36.P9 (VSS), U36.T1 (VSS), U36.T9 (VSS); also elsewhere on the board
unnamed: R180.1, U36.L8 (ZQ)

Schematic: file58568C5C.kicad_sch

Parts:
C232, C233: C_2.2u; C_0603; MFG Part# CC0603MRX5R5BB225
C234, C235, C236, C238, C239: C_0.1u; C_0603; MFG Part# C0603C104K4RACTU
C237: C_10n; C_0402; MFG Part# 885012205012
D53: MCP1501-18; SOT23-6; MFG Part# MCP1501T-18E/CHY
R152, R154, R155, R156, R157, R158, R159, R160, R161: R_1.02k; R_0603; MFG Part# ERJ-3EKF1021V
R153: R_56R; R_0603; MFG Part# ERJ-3EKF56R0V
U7: AZ4558C; SOIC8; MFG Part# AZ4558CMTR-E1
U33: MAX5501; SSOP20; MFG Part# MAX5501BGAP+
U34, U35: OPA692; SOT23-6; MFG Part# OPA692IDBVT

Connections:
1.8V_REF: D53.1 (OUT), R152.1, R153.1, R154.2, R155.2, U33.6 (REFAB), U33.15 (REFCD), U34.4 (IN-), U35.4 (IN-)
+3V3_VA: C236.1, C237.1, U33.7 (~CL), U33.14 (~PDL), U33.20 (VDD)
-Va: U7.4 (V-), U34.2 (-VS), U35.2 (-VS); also elsewhere on the board
CH1_GAIN: C235.1, R159.1; also elsewhere on the board
CH1_GAIN_ADJ: U7.5 (+), U33.16 (FBC), U33.17 (OUTC)
CH1_OFFSET: U35.1 (OUT); also elsewhere on the board
CH1_OFFSET_ADJ: R161.2, U33.2 (FBA), U33.3 (OUTA)
CH2_GAIN: C234.1, R158.1; also elsewhere on the board
CH2_GAIN_ADJ: U7.3 (+), U33.18 (OUTD), U33.19 (FBD)
CH2_OFFSET: U34.1 (OUT); also elsewhere on the board
CH2_OFFSET_ADJ: R160.2, U33.4 (OUTB), U33.5 (FBB)
DASCLK: U33.10 (SCLK); also elsewhere on the board
DASDIN: U33.9 (DIN); also elsewhere on the board
DASYNC: U33.8 (~CS); also elsewhere on the board
GND: C232.2, C233.2, C234.2, C235.2, C236.2, C237.2, C238.2, C239.2, D53.2 (GND), D53.3 (GND), D53.5 (GND), R152.2, U33.1 (AGND), U33.11 (DGND); also elsewhere on the board
unnamed: C233.1, R153.2
unnamed: R154.1, R156.2, U7.2 (-)
unnamed: R156.1, R158.2, U7.1
unnamed: R155.1, R157.2, U7.6 (-)
unnamed: R157.1, R159.2, U7.7
unnamed: C238.1, R160.1, U34.3 (IN+)
unnamed: C239.1, R161.1, U35.3 (IN+)
PWR_EN: U33.13 (UPO)
Va: C232.1, D53.4 (SHDN#), D53.6 (VDD), U7.8 (V+), U34.6 (+VS), U35.6 (+VS); also elsewhere on the board
